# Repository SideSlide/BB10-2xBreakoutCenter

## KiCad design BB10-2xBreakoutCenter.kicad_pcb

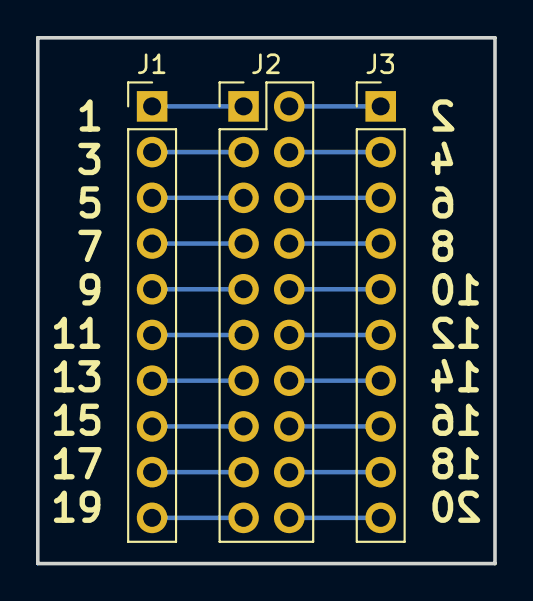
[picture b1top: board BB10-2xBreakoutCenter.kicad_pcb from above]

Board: 2 copper layers, 25.4 x 29.2 mm, 3 parts (0 on the bottom side), 20 nets.

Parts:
J1, J3: Conn_01x10; PinHeader_1x10_P2.54mm_Vertical
J2: Conn_02x10_Odd_Even; PinHeader_2x10_P2.54mm_Vertical

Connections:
unnamed: J1.1, J2.1
unnamed: J1.2, J2.3
unnamed: J1.3, J2.5
unnamed: J1.4, J2.7
unnamed: J1.5, J2.9
unnamed: J1.6, J2.11
unnamed: J1.7, J2.13
unnamed: J1.8, J2.15
unnamed: J1.9, J2.17
unnamed: J1.10, J2.19
unnamed: J2.2, J3.1
unnamed: J2.4, J3.2
unnamed: J2.6, J3.3
unnamed: J2.8, J3.4
unnamed: J2.10, J3.5
unnamed: J2.12, J3.6
unnamed: J2.14, J3.7
unnamed: J2.16, J3.8
unnamed: J2.18, J3.9
unnamed: J2.20, J3.10

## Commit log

2018-10-17 Invert back silkscreen
